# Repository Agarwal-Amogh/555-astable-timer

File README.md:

# 555 Timer Astable Multivibrator

## Overview
A 555 timer configured in astable mode designed using KiCad and verified using LTspice.

## Features
- LTspice simulation
- KiCad schematic
- PCB layout
- Gerber files
- Through-hole components

## Tools Used
- KiCad 9
- LTspice

## Circuit

## Simulation

## PCB

## Future Improvements
- Add power LED
- Add mounting holes
- Ground plane

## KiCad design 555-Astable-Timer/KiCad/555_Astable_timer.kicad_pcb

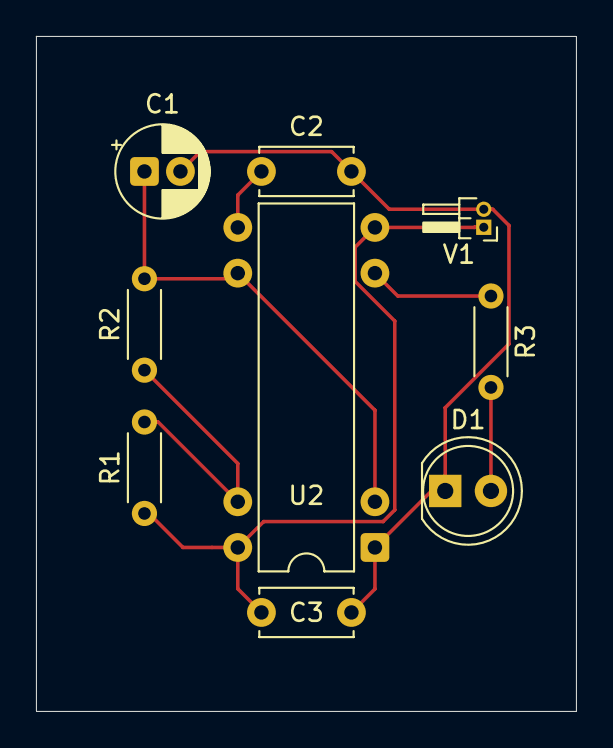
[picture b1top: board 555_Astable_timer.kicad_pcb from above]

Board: 2 copper layers, 30.0 x 37.5 mm, 9 parts (0 on the bottom side), 7 nets.

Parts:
C1: 10u; CP_Radial_D5.0mm_P2.00mm
C2, C3: 100n; C_Disc_D5.0mm_W2.5mm_P5.00mm
D1: LED; LED_D5.0mm
R1, R2: 150k; R_Axial_DIN0204_L3.6mm_D1.6mm_P5.08mm_Horizontal
R3: 470; R_Axial_DIN0204_L3.6mm_D1.6mm_P5.08mm_Horizontal
U2: NE555D; DIP-8-16_W7.62mm
V1: 9; PinHeader_1x02_P1.00mm_Horizontal

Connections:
/DISCHARGE: R1.2, R2.1, U2.7 (DISCH)
/OUT: R3.1, U2.3 (OUT)
/TIMING: C1.1, R2.2, U2.2 (TRIG), U2.6 (THRES)
GND: C1.2, C2.2, C3.2, D1.1 (K), U2.1 (GND), V1.2
unnamed: D1.2 (A), R3.2
unnamed: C2.1, U2.5 (CONT)
VCC: C3.1, R1.1, U2.4 (~RST), U2.8 (VCC), V1.1
